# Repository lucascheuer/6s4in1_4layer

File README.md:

# 6s4in1
6s 4in1 ESC with low amperage

This version has moved to 4 layers to increase the current capability from the original version

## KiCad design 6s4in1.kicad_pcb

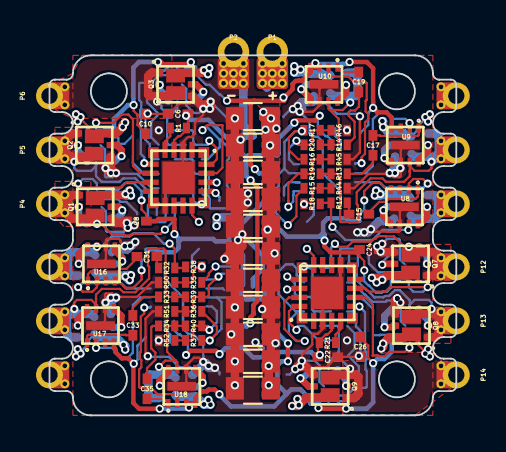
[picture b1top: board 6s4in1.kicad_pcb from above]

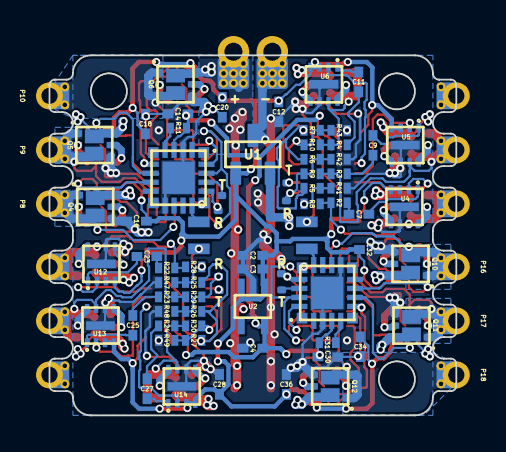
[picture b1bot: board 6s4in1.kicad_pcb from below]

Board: 4 copper layers, 22.6 x 20.0 mm, 154 parts (81 on the bottom side), 104 nets.

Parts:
C1, C5, C13, C21, C29, C37, C38, C39, C40, C41, C42: 10uF; C_0805
C2: 10uF; C_0402
C3, C4, C6, C14, C22, C30: 4.7uF; C_0402
C7, C8, C9, C10, C11, C12, C15, C16, C17, C18, C19, C20, C23, C24, C25, C26, C27, C28, C31, C32, C33, C34, C35, C36: 1uF; C_0402
P1, P2: Pad; PowerPad
P3, P7, P11, P15: Pad; RCPad
P4, P5, P6, P8, P9, P10, P12, P13, P14, P16, P17, P18: Pad; PhasePad
P19, P20, P21, P22: Pad; HOLE
P23, P24, P25, P26, P27, P28, P29, P30: Pad; FlashPad
Q1, Q2, Q3, Q4, Q5, Q6, Q7, Q8, Q9, Q10, Q11, Q12: NTLUD4C26N; UDFN6-NTLUD4
R1, R11, R21, R31: 1k; R_0402
R2, R3, R4, R12, R13, R14, R22, R23, R24, R32, R33, R34: 1; R_0402
R5, R6, R7, R15, R16, R17, R25, R26, R27, R35, R36, R37, R41, R42, R43, R44, R45, R46, R47, R48, R49, R50, R51, R52: 10k; R_0402
R8, R9, R10, R18, R19, R20, R28, R29, R30, R38, R39, R40: 100k; R_0402
U1: LM3480IM3-5.0; SOT-23-3
U2: TLV70033; SC-70-5
U3, U7, U11, U15: EFM8BB21-QFN20; QFN20
U4, U5, U6, U8, U9, U10, U12, U13, U14, U16, U17, U18: TPS51604; 8-WFDFN

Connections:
3.3V: C4.1, C6.2, C14.2, C22.2, C30.2, R1.2, R11.2, R21.2, R31.2, U2.5, U3.4, U7.4, U11.4, U15.4
5V: C2.2, C3.1, C8.2, C10.2, C12.2, C16.2, C18.2, C20.2, C24.2, C26.2, C28.2, C32.2, C34.2, C36.2, U1.1, U2.1, U2.3, U4.3, U4.4, U5.3, U5.4, U6.3, U6.4, U8.3, U8.4, U9.3, U9.4, U10.3, U10.4, U12.3, U12.4, U13.3, U13.4, U14.3, U14.4, U16.3, U16.4, U17.3, U17.4, U18.3, U18.4
/ESC_1/BST_A: C11.1, R4.2
/ESC_1/BST_B: C9.1, R3.2
/ESC_1/BST_C: C7.1, R2.2
/ESC_1/HIGH_A: Q3.2, U6.8
/ESC_1/HIGH_B: Q2.2, U5.8
/ESC_1/HIGH_C: Q1.2, U4.8
/ESC_1/LOW_A: Q3.5, U6.5
/ESC_1/LOW_B: Q2.5, U5.5
/ESC_1/LOW_C: Q1.5, U4.5
/ESC_1/PHASEGND: R5.2, R6.2, R7.2, U3.19
/ESC_1/PHASE_A: P6.~, Q3.1, Q3.3, R4.1, R10.1, U6.7
/ESC_1/PHASE_B: P5.~, Q2.1, Q2.3, R3.1, R9.1, U5.7
/ESC_1/PHASE_C: P4.~, Q1.1, Q1.3, R2.1, R8.1, U4.7
/ESC_1/PWM_A: U3.7, U6.2
/ESC_1/PWM_B: U3.8, U5.2
/ESC_1/PWM_C: U3.9, U4.2
/ESC_1/Rcp_in: P3.~, U3.15
/ESC_1/SEN_A: R7.1, R10.2, R43.1, U3.20
/ESC_1/SEN_B: P24.~, R6.1, R9.2, R42.1, U3.17
/ESC_1/SEN_C: R5.1, R8.2, R41.1, U3.16
/ESC_2/BST_A: C19.1, R14.2
/ESC_2/BST_B: C17.1, R13.2
/ESC_2/BST_C: C15.1, R12.2
/ESC_2/HIGH_A: Q6.2, U10.8
/ESC_2/HIGH_B: Q5.2, U9.8
/ESC_2/HIGH_C: Q4.2, U8.8
/ESC_2/LOW_A: Q6.5, U10.5
/ESC_2/LOW_B: Q5.5, U9.5
/ESC_2/LOW_C: Q4.5, U8.5
/ESC_2/PHASEGND: R15.2, R16.2, R17.2, U7.19
/ESC_2/PHASE_A: P10.~, Q6.1, Q6.3, R14.1, R20.1, U10.7
/ESC_2/PHASE_B: P9.~, Q5.1, Q5.3, R13.1, R19.1, U9.7
/ESC_2/PHASE_C: P8.~, Q4.1, Q4.3, R12.1, R18.1, U8.7
/ESC_2/PWM_A: U7.7, U10.2
/ESC_2/PWM_B: U7.8, U9.2
/ESC_2/PWM_C: U7.9, U8.2
/ESC_2/Rcp_in: P7.~, U7.15
/ESC_2/SEN_A: R17.1, R20.2, R46.1, U7.20
/ESC_2/SEN_B: P26.~, R16.1, R19.2, R45.1, U7.17
/ESC_2/SEN_C: R15.1, R18.2, R44.1, U7.16
/ESC_3/BST_A: C27.1, R24.2
/ESC_3/BST_B: C25.1, R23.2
/ESC_3/BST_C: C23.1, R22.2
/ESC_3/HIGH_A: Q9.2, U14.8
/ESC_3/HIGH_B: Q8.2, U13.8
/ESC_3/HIGH_C: Q7.2, U12.8
/ESC_3/LOW_A: Q9.5, U14.5
/ESC_3/LOW_B: Q8.5, U13.5
/ESC_3/LOW_C: Q7.5, U12.5
/ESC_3/PHASEGND: R25.2, R26.2, R27.2, U11.19
/ESC_3/PHASE_A: P14.~, Q9.1, Q9.3, R24.1, R30.1, U14.7
/ESC_3/PHASE_B: P13.~, Q8.1, Q8.3, R23.1, R29.1, U13.7
/ESC_3/PHASE_C: P12.~, Q7.1, Q7.3, R22.1, R28.1, U12.7
/ESC_3/PWM_A: U11.7, U14.2
/ESC_3/PWM_B: U11.8, U13.2
/ESC_3/PWM_C: U11.9, U12.2
/ESC_3/Rcp_in: P11.~, U11.15
/ESC_3/SEN_A: R27.1, R30.2, R49.1, U11.20
/ESC_3/SEN_B: P28.~, R26.1, R29.2, R48.1, U11.17
/ESC_3/SEN_C: R25.1, R28.2, R47.1, U11.16
/ESC_4/BST_A: C35.1, R34.2
/ESC_4/BST_B: C33.1, R33.2
/ESC_4/BST_C: C31.1, R32.2
/ESC_4/HIGH_A: Q12.2, U18.8
/ESC_4/HIGH_B: Q11.2, U17.8
/ESC_4/HIGH_C: Q10.2, U16.8
/ESC_4/LOW_A: Q12.5, U18.5
/ESC_4/LOW_B: Q11.5, U17.5
/ESC_4/LOW_C: Q10.5, U16.5
/ESC_4/PHASEGND: R35.2, R36.2, R37.2, U15.19
/ESC_4/PHASE_A: P18.~, Q12.1, Q12.3, R34.1, R40.1, U18.7
/ESC_4/PHASE_B: P17.~, Q11.1, Q11.3, R33.1, R39.1, U17.7
/ESC_4/PHASE_C: P16.~, Q10.1, Q10.3, R32.1, R38.1, U16.7
/ESC_4/PWM_A: U15.7, U18.2
/ESC_4/PWM_B: U15.8, U17.2
/ESC_4/PWM_C: U15.9, U16.2
/ESC_4/Rcp_in: P15.~, U15.15
/ESC_4/SEN_A: R37.1, R40.2, R52.1, U15.20
/ESC_4/SEN_B: P30.~, R36.1, R39.2, R51.1, U15.17
/ESC_4/SEN_C: R35.1, R38.2, R50.1, U15.16
GND: C1.2, C2.1, C3.2, C4.2, C5.2, C6.1, C8.1, C10.1, C12.1, C13.2, C14.1, C16.1, C18.1, C20.1, C21.2, C22.1, C24.1, C26.1, C28.1, C29.2, C30.1, C32.1, C34.1, C36.1, C37.2, C38.2, C39.2, C40.2, C41.2, C42.2, P2.~, Q1.4, Q2.4, Q3.4, Q4.4, Q5.4, Q6.4, Q7.4, Q8.4, Q9.4, Q10.4, Q11.4, Q12.4, R41.2, R42.2, R43.2, R44.2, R45.2, R46.2, R47.2, R48.2, R49.2, R50.2, R51.2, R52.2, U1.3, U2.2, U3.3, U3.12, U3.21, U4.6, U4.9, U5.6, U5.9, U6.6, U6.9, U7.3, U7.12, U7.21, U8.6, U8.9, U9.6, U9.9, U10.6, U10.9, U11.3, U11.12, U11.21, U12.6, U12.9, U13.6, U13.9, U14.6, U14.9, U15.3, U15.12, U15.21, U16.6, U16.9, U17.6, U17.9, U18.6, U18.9
unnamed: C7.2, U4.1
unnamed: C9.2, U5.1
unnamed: C11.2, U6.1
unnamed: C15.2, U8.1
unnamed: C17.2, U9.1
unnamed: C19.2, U10.1
unnamed: C23.2, U12.1
unnamed: C25.2, U13.1
unnamed: C27.2, U14.1
unnamed: C31.2, U16.1
unnamed: C33.2, U17.1
unnamed: C35.2, U18.1
unnamed: P23.~, U3.18
unnamed: P25.~, U7.18
unnamed: P27.~, U11.18
unnamed: P29.~, U15.18
unnamed: R1.1, U3.5
unnamed: R11.1, U7.5
unnamed: R21.1, U11.5
unnamed: R31.1, U15.5
VCC: C1.1, C5.1, C13.1, C21.1, C29.1, C37.1, C38.1, C39.1, C40.1, C41.1, C42.1, P1.~, Q1.6, Q2.6, Q3.6, Q4.6, Q5.6, Q6.6, Q7.6, Q8.6, Q9.6, Q10.6, Q11.6, Q12.6, U1.2

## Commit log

2019-01-12 Finished Routing
2019-01-14 Added Tx/Rx labels and +/- labels
2019-01-14 cleaning up for public
2019-01-14 removed backups and fishpepper's stuff
2019-01-14 moved
2019-01-14 Added License for public release
2019-01-14 Added reason for 4 layer
